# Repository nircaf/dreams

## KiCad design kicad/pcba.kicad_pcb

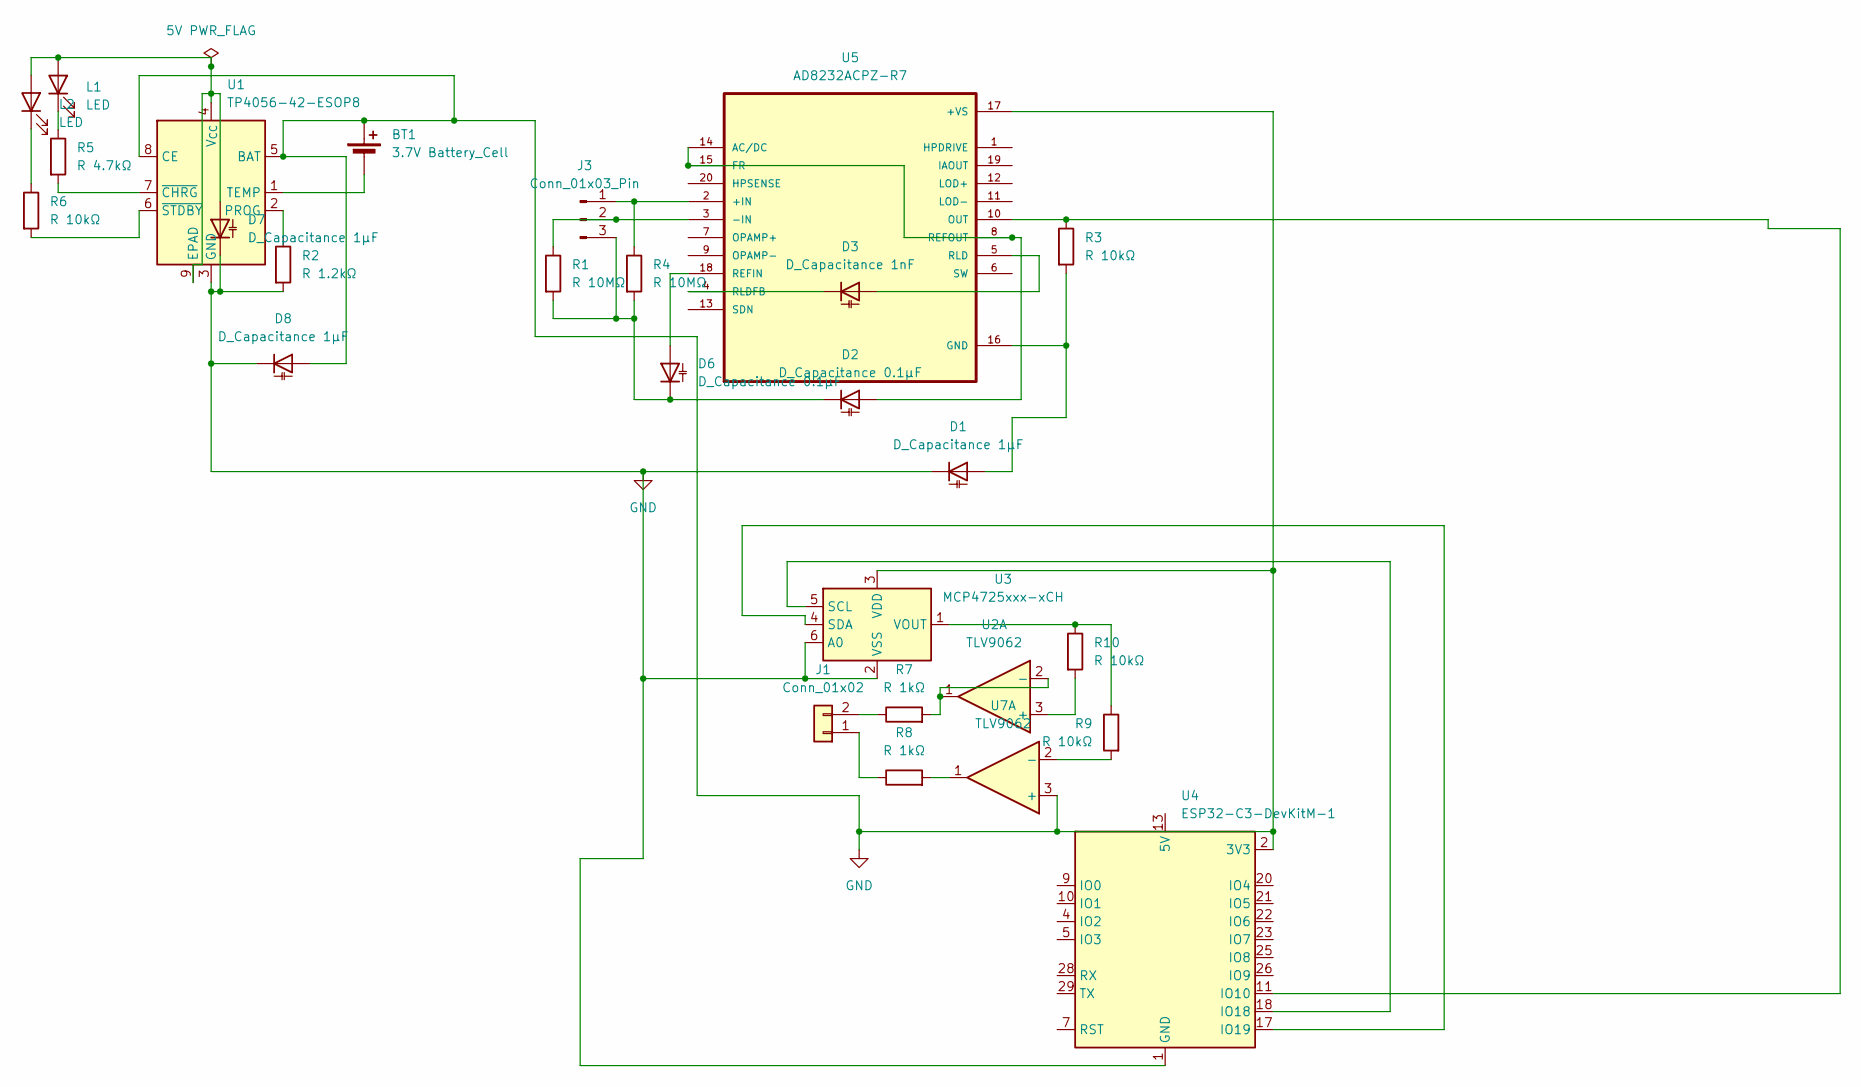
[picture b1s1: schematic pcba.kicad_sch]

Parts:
BT1: 3.7V Battery_Cell; JST_PH_S2B-PH-K_1x02_P2.00mm_Horizontal
D1, D7, D8: D_Capacitance 1µF; C_0603_1608Metric
D2, D6: D_Capacitance 0.1µF; C_0603_1608Metric
D3: D_Capacitance 1nF; C_0603_1608Metric
J1: Conn_01x02; PinHeader_1x02_P2.54mm_Vertical
J3: Conn_01x03_Pin; JST_EH_B3B-EH-A_1x03_P2.50mm_Vertical
L1, L2: LED; LED_D3.0mm
R1, R4: R 10MΩ; R_0805_2012Metric
R2: R 1.2kΩ; R_0805_2012Metric
R3, R6, R9, R10: R 10kΩ; R_0805_2012Metric
R5: R 4.7kΩ; R_0805_2012Metric
R7, R8: R 1kΩ; R_0805_2012Metric
U1: TP4056-42-ESOP8; SOIC-8-1EP_3.9x4.9mm_P1.27mm_EP2.41x3.3mm_ThermalVias
U2, U7: TLV9062; SOIC-8_3.9x4.9mm_P1.27mm
U3: MCP4725xxx-xCH; SOT-23-6
U4: ESP32-C3-DevKitM-1
U5: AD8232ACPZ-R7; SOIC-20W_7.5x12.8mm_P1.27mm

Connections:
GND: BT1.1 (+), D1.1 (K), D7.1 (K), D8.1 (K), D8.2 (A), R2.2, U1.3 (GND), U1.5 (BAT), U1.8 (CE), U3.2 (VSS), U3.3 (VDD), U3.6 (A0), U4.1 (GND), U4.2 (3V3), U4.3 (3V3), U4.6 (GND), U4.8 (GND), U4.12 (GND), U4.15 (GND), U4.16 (GND), U4.19 (GND), U4.24 (GND), U4.27 (GND), U4.30 (GND), U5.17 (+VS), U7.3 (+)
unnamed: BT1.2 (-), U1.1 (TEMP)
unnamed: D1.2 (A), R3.2, U5.16 (GND)
unnamed: D2.2 (A), U5.8 (REFOUT), U5.14 (AC/DC), U5.15 (FR)
unnamed: D2.1 (K), D6.1 (K), J3.3, R1.2, R4.2
unnamed: D3.2 (A), U5.5 (RLD)
unnamed: D3.1 (K), U5.4 (RLDFB)
unnamed: D6.2 (A), U5.18 (REFIN)
unnamed: D7.2 (A), L1.2 (A), L2.2 (A), U1.4 (V_{CC}), U1.9 (EPAD)
unnamed: J1.1, R8.1
unnamed: J1.2, R7.1
unnamed: J3.1, R4.1, U5.2 (+IN)
unnamed: J3.2, R1.1, U5.3 (-IN)
unnamed: L1.1 (K), R5.1
unnamed: L2.1 (K), R6.1
unnamed: R8.2, U7.1
unnamed: R2.1, U1.2 (PROG)
unnamed: R5.2, U1.7 (~CHRG)
unnamed: R6.2, U1.6 (~STDBY)
unnamed: R10.2, U2.3 (+)
unnamed: R7.2, U2.1, U2.2 (-)
unnamed: U3.5 (SCL), U4.18 (IO18)
unnamed: U3.4 (SDA), U4.17 (IO19)
unnamed: R9.1, R10.1, U3.1 (VOUT)
unnamed: U4.13 (5V), U4.14 (5V)
unnamed: R3.1, U4.11 (IO10), U5.10 (OUT)
unnamed: R9.2, U7.2 (-)

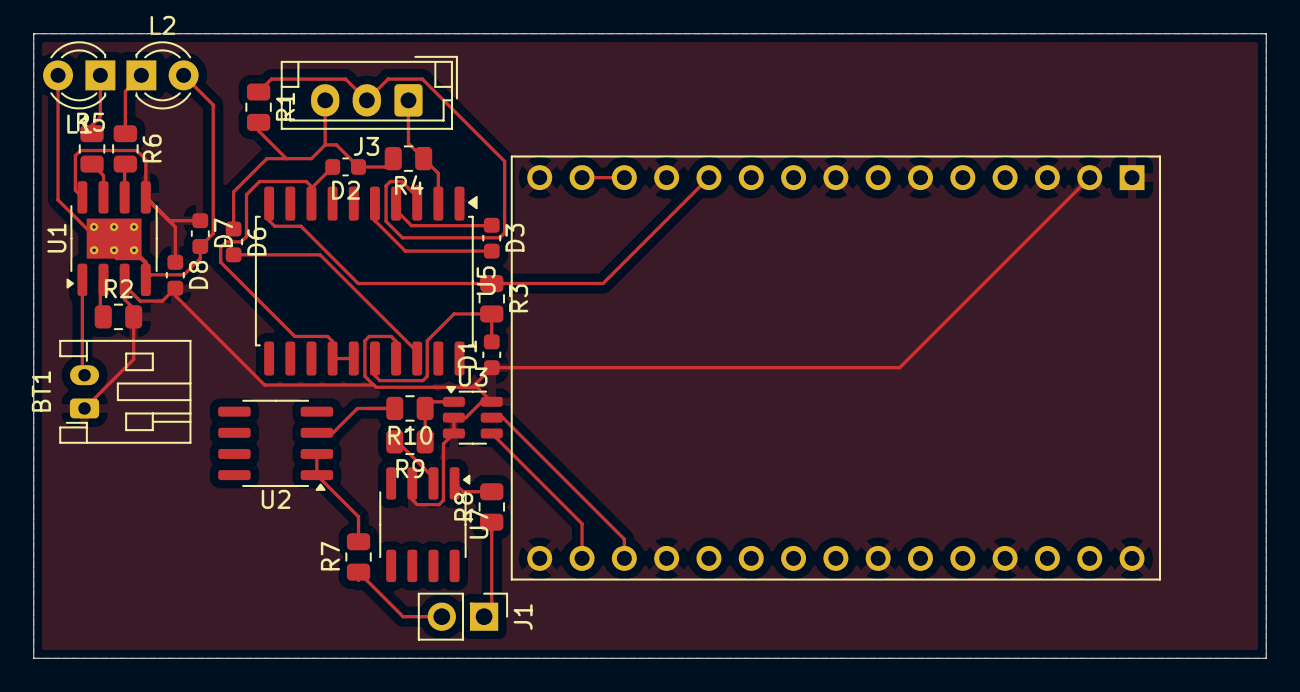
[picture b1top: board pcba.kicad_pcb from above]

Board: 2 copper layers, 74.0 x 37.5 mm, 27 parts (0 on the bottom side), 27 nets.

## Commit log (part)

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2025-06-18 gallery replace
2025-06-18 glry
2025-09-18 auto vid
2025-09-24 Add SEO-focused blog hub for HypnoDreamz
2025-09-24 Create assets hub with clinical resources and schema
2025-09-24 Move FAQ and trials hub to assets page
2025-09-24 Add Google site verification meta tag
2025-09-24 Add assets and SEO enhancements
2025-09-24 Add SEO-focused blog hub for HypnoDreamz (#1)
    * Add SEO-focused blog hub for HypnoDreamz
    * Create assets hub with clinical resources and schema
    * Move FAQ and trials hub to assets page
    * Add Google site verification meta tag
    * a
    * Add assets and SEO enhancements
2025-09-24 Add sitemap.xml with homepage and assets entries
2025-09-24 Add missing product structured data details
2025-09-24 Add missing product structured data details (#2)
2025-09-24 feat: set favicon to link_icon.png in index.html
2025-09-25 feat: improve favicon support and add robots.txt for SEO
2025-09-25 Add Google tag (gtag.js) to all pages
2025-10-10 Add personalized and customized stimulation messaging throughout website
    - Updated hero section to emphasize personalization to unique needs
    - Modified feature cards to highlight personalized tVNS technology, anxiety reduction, and sleep enhancement
    - Enhanced how-it-works section with personalized stimulation and adaptive neural relaxation
    - Updated meta descriptions and keywords to include personalization terms
    - Emphasized that stimulation adapts to individual physiology, stress patterns, and sleep architecture
2025-10-16 Update waitlist form to use Tally with simplified parameters
    - Replaced Google Forms iframe with Tally form
    - Added Tally embed script for dynamic loading
    - Simplified parameters to alignLeft=1, hideTitle=1, dynamicHeight=1
    - Removed fallback link and extra styling parameters
    - Form now uses Tally.so for better integration
2025-12-14 Update logo with animated mask effect - blue color with smooth fade in/out transitions
2026-02-11 Enhance science dashboard: remove product example, fix local CORS, update UI
2026-02-18 Update from local
2026-02-27 Configure Vercel deployment with dreamz.html
2026-02-27 Configure Render static site with index.html redirect
2026-02-27 Remove render.yaml to stop auto-detecting Python service
2026-02-27 Add empty requirements.txt to satisfy Render Python detection
2026-02-27 Add minimal Python HTTP server for Render
2026-03-05 Remove WebGL filler placeholder
2026-03-05 Fix Google Search Console JSON-LD schema issues
2026-03-05 fix: never show placeholder shape in carousel canvas, only show mask GLB
2026-03-06 Add new NSDR blog card to blog index (post 16)
2026-03-06 Add Dreamz social voice guide for content consistency
2026-03-08 Show custom cursor only on Windows/macOS desktop
2026-03-08 Disable custom cursor on iOS/Android and show only on desktop
2026-03-08 Move terms/privacy links to bottom footer
2026-03-08 Keep terms/privacy links only in bottom footer
2026-03-08 Remove Dreamz mask carousel description text
2026-03-08 Keep terms/privacy links only in bottom-most footer
2026-03-11 Update website files
2026-03-12 Remove em dash from hero subtitle copy
2026-03-12 Add new Dreamz logo favicon and touch icons across site
2026-03-12 Update favicon and thumbnail assets to non-background logo
2026-04-23 Update site branding assets and logos
2026-04-30 Add contact page and legal links
2026-04-30 Share site navigation and footer chrome
2026-05-01 Fix mobile card clipping
2026-05-03 Add preorder flow and site polish
2026-05-05 Add preorder flow and animated logo
    - Add preorder page with full flow
    - Update logo to animated canvas based on cascade animation
    - Site polish: shared navigation/footer improvements, blog/research page updates
    - Add start-server.bat for local dev convenience
2026-05-14 Update landing hero and split content pages
2026-05-14 Add account deletion page
